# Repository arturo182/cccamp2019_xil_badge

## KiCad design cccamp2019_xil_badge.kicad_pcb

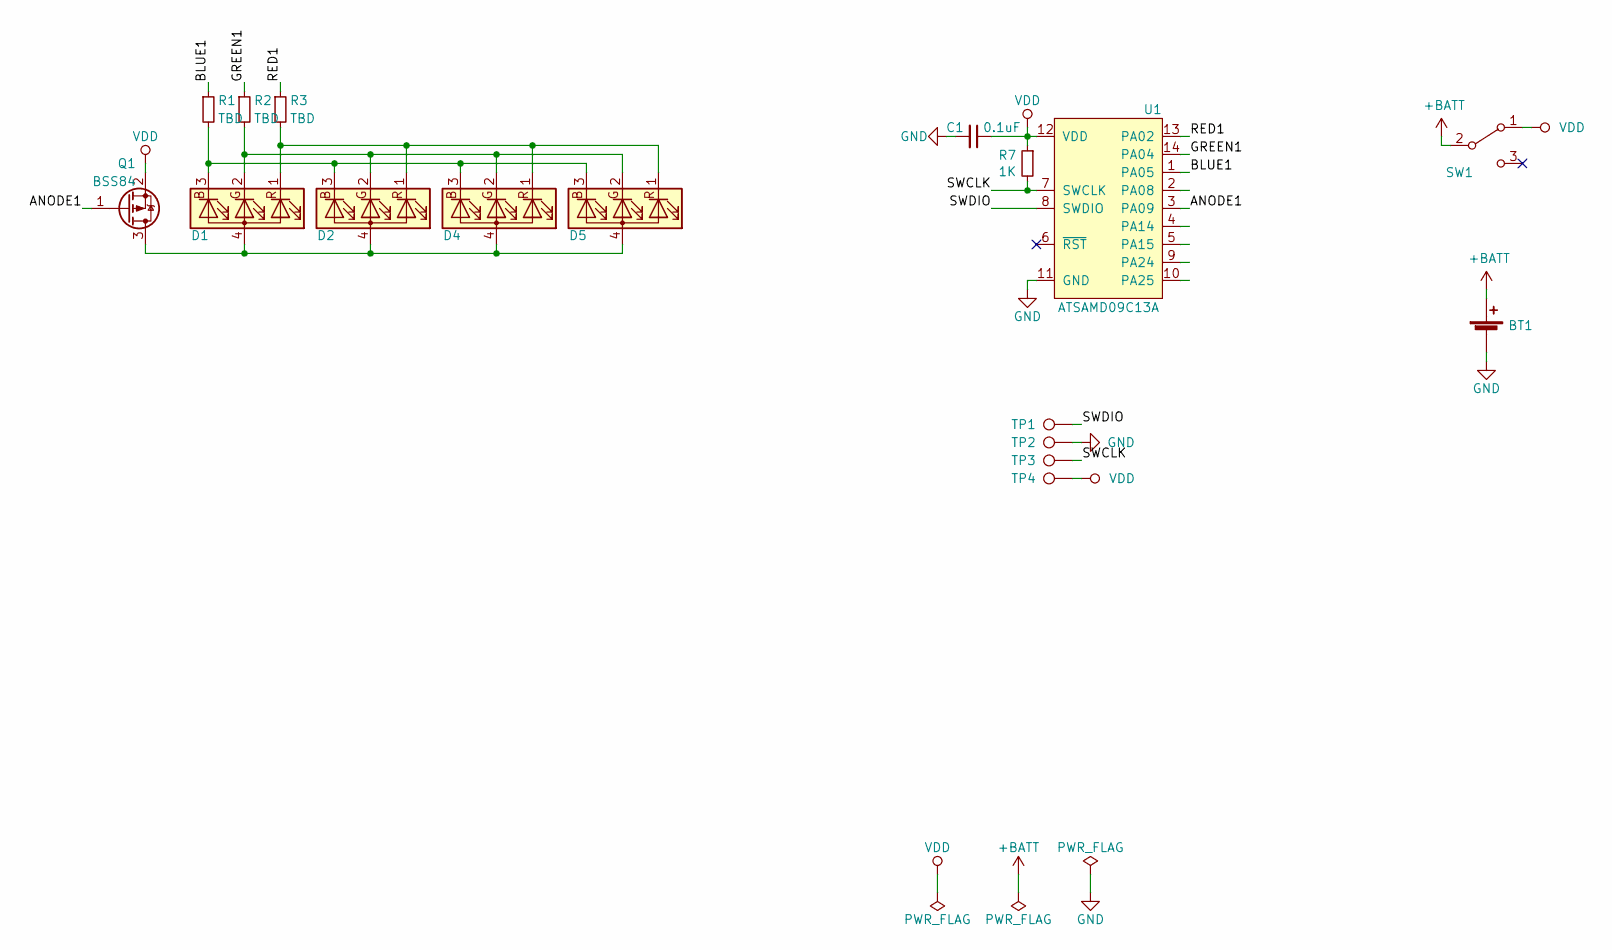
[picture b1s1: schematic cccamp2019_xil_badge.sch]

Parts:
BT1: Battery_Cell; CR1632
C1: 0.1uF; C_0603_1608Metric
D1, D2, D4, D5: LED_RGBA; LED_RGBA_0606_UpsideDown
Q1: BSS84; SOT-23
R1, R2, R3: TBD; R_0603_1608Metric
R7: 1K; R_0603_1608Metric
SW1: SW_SPDT; SW_SPDT_PCM12
TP1: TP_SWDIO; TestPoint_Pad_D1.0mm
TP2: TP_GND; TestPoint_Pad_D1.0mm
TP3: TP_SWCLK; TestPoint_Pad_D1.0mm
TP4: TP_VDD; TestPoint_Pad_D1.0mm
U1: ATSAMD09C13A; SOIC-14_3.9x8.7mm_P1.27mm

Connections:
+BATT: BT1.1 (+), SW1.2 (B)
/ANODE1: Q1.1 (G), U1.3 (PA09)
/BLUE1: R1.1, U1.1 (PA05)
/GREEN1: R2.1, U1.14 (PA04)
/RED1: R3.1, U1.13 (PA02)
/SWCLK: R7.2, TP3.1, U1.7 (SWCLK)
/SWDIO: TP1.1, U1.8 (SWDIO)
GND: BT1.2 (-), C1.2, TP2.1, U1.11 (GND)
unnamed: D1.1 (RK), D2.1 (RK), D4.1 (RK), D5.1 (RK), R3.2
unnamed: D1.2 (GK), D2.2 (GK), D4.2 (GK), D5.2 (GK), R2.2
unnamed: D1.3 (BK), D2.3 (BK), D4.3 (BK), D5.3 (BK), R1.2
unnamed: D1.4 (A), D2.4 (A), D4.4 (A), D5.4 (A), Q1.3 (D)
VDD: C1.1, Q1.2 (S), R7.1, SW1.1 (A), TP4.1, U1.12 (VDD)

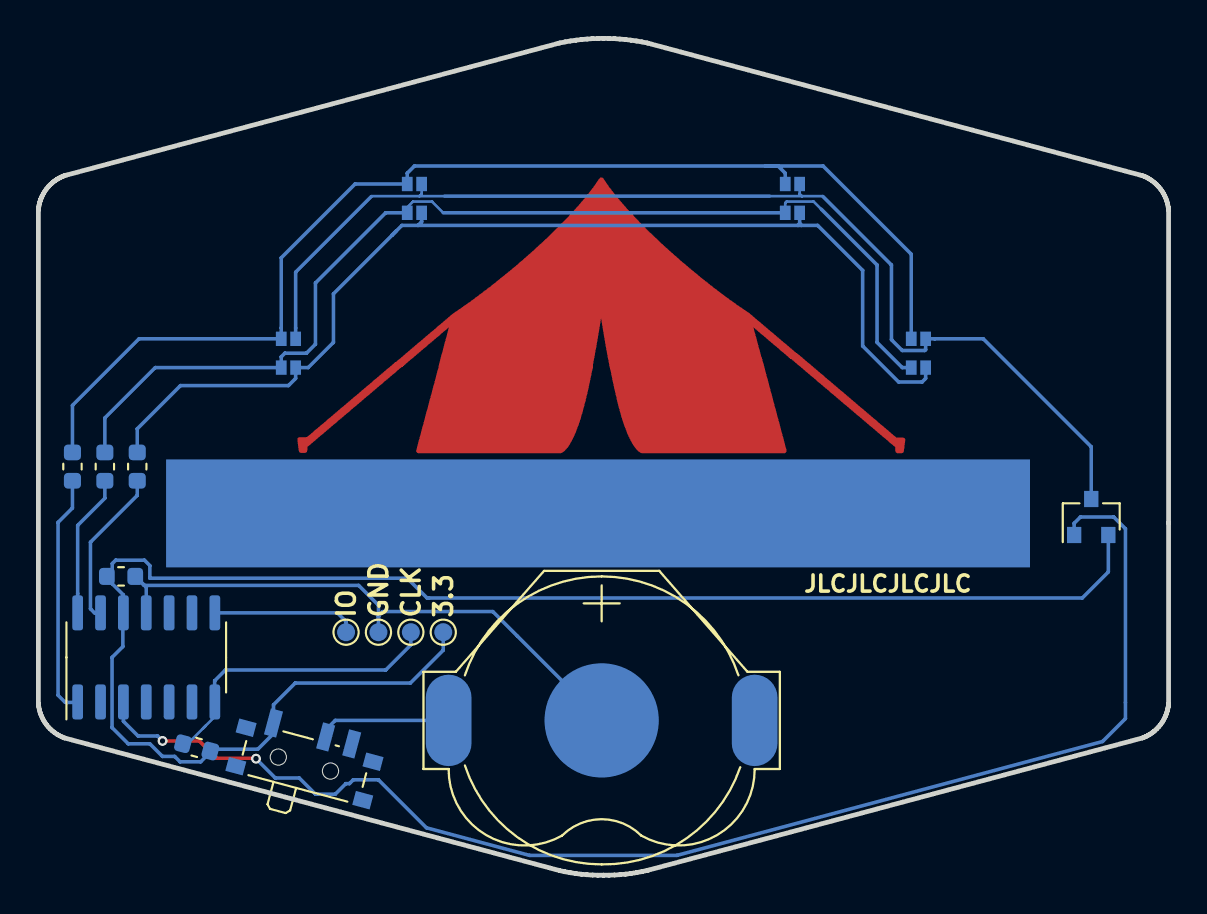
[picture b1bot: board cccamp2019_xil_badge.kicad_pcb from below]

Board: 2 copper layers, 62.8 x 46.5 mm, 17 parts (17 on the bottom side), 13 nets.

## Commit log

2019-06-06 Initial WIP
2019-07-03 More work
